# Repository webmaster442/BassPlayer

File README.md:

# BassPlayer

An Audio Player based on bass.dll components & a Total Commander lister plugin.

Compiled binary can be downloaded from: https://drive.google.com/folderview?id=0BzRxNHSnXbB5fjc0bHhQZU4tWXhuWFFHWDBHcWtfVzgtRnJ0d2lVZURTMXZnUmtfV1UwNmc&usp=sharing 

##Features

 - Supports various audio formats: MP3, MP4, AAC, OGG, WAV, FLAC, WavPack, Apple Lossless (ALAC), WMA, AC3, CDDA
 - Supports various playlist formats: PLS, M3U, WPL (Windows Media Player playlists), BPL (Player's native playlist format)
 - 32 bit and 64 bit support
 - Integrated file browser
 - Supports browsing of iTunes database (iTunes required)
 - Supports Windows 7 & 8 Shell features: Taskbar progress & Taskbar preview buttons
 - Supports Keyboard media keys
 - Media Library
 - Mini Player view
 - Audio Converter tools
 
## Required tools to compile
 - Visual Studio Community edition
 - Bass.net API -> http://bass.radio42.com/

##Requirements to run
 - .NET Framework 4.5 (Window7 & Windows8 & Windows 8.1)
   http://www.microsoft.com/hu-hu/download/details.aspx?id=30653

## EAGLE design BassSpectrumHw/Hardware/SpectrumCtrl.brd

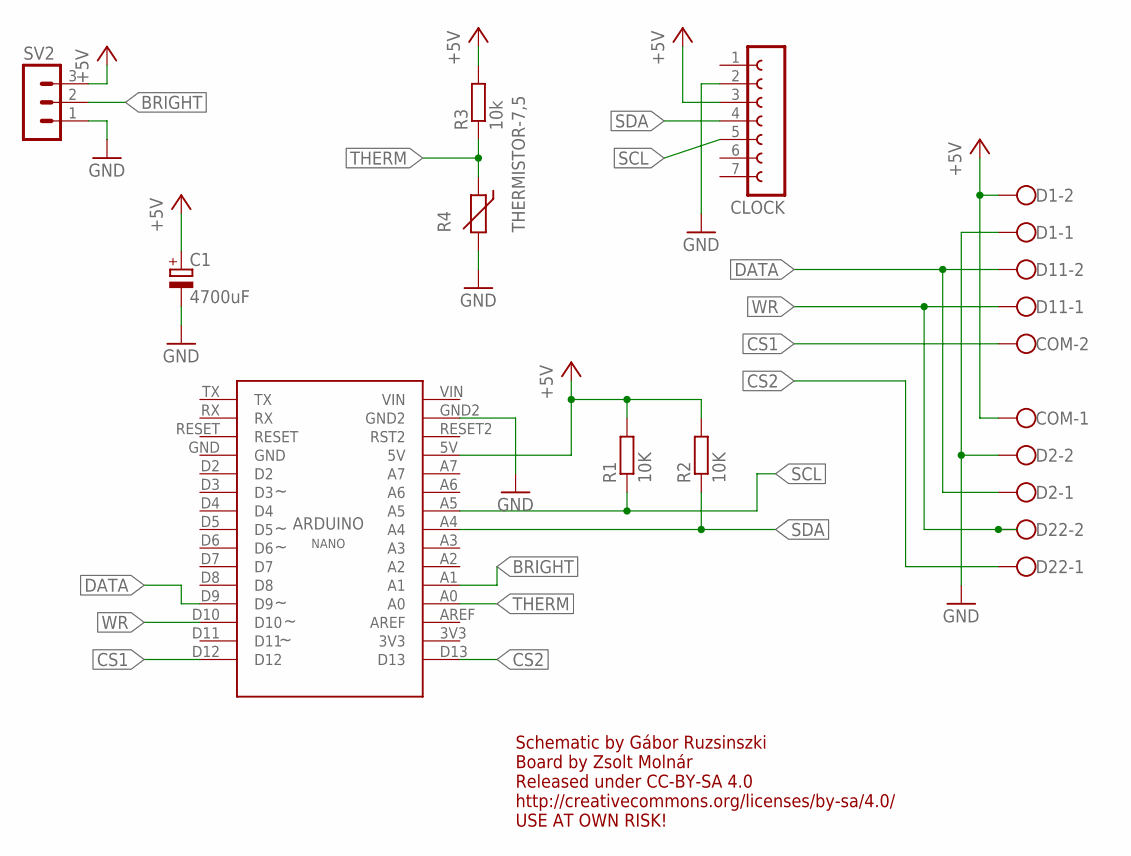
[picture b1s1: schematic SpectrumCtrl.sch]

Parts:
C1: 4700uF; E7,5-16
CLOCK: FE07-1; FE07
COM: W237-102
D1, D2, D11, D22: W237-102
R1, R2: 10K; 0309/12
R3: 10k; 0309/12
R4: THERMISTOR-7,5; R-7,5
SV2: MA03-1
U$1: NANO

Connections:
+5V: C1.+, CLOCK.3, COM.1, D1.2, R1.2, R2.2, R3.2, SV2.3, U$1.5V
BRIGHT: SV2.2, U$1.A1
CS1: COM.2, U$1.D12
CS2: D22.1, U$1.D13
DATA: D2.1, D11.2, U$1.D9
GND: C1.-, CLOCK.2, D1.1, D2.2, R4.2, SV2.1, U$1.GND2
SCL: CLOCK.5, R1.1, U$1.A5
SDA: CLOCK.4, R2.1, U$1.A4
THERM: R3.1, R4.1, U$1.A0
WR: D11.1, D22.2, U$1.D10

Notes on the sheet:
Schematic by Gábor Ruzsinszki Board by Zsolt Molnár Released under CC-BY-SA 4.0 http://creativecommons.org/licenses/by-sa/4.0/ USE AT OWN RISK!

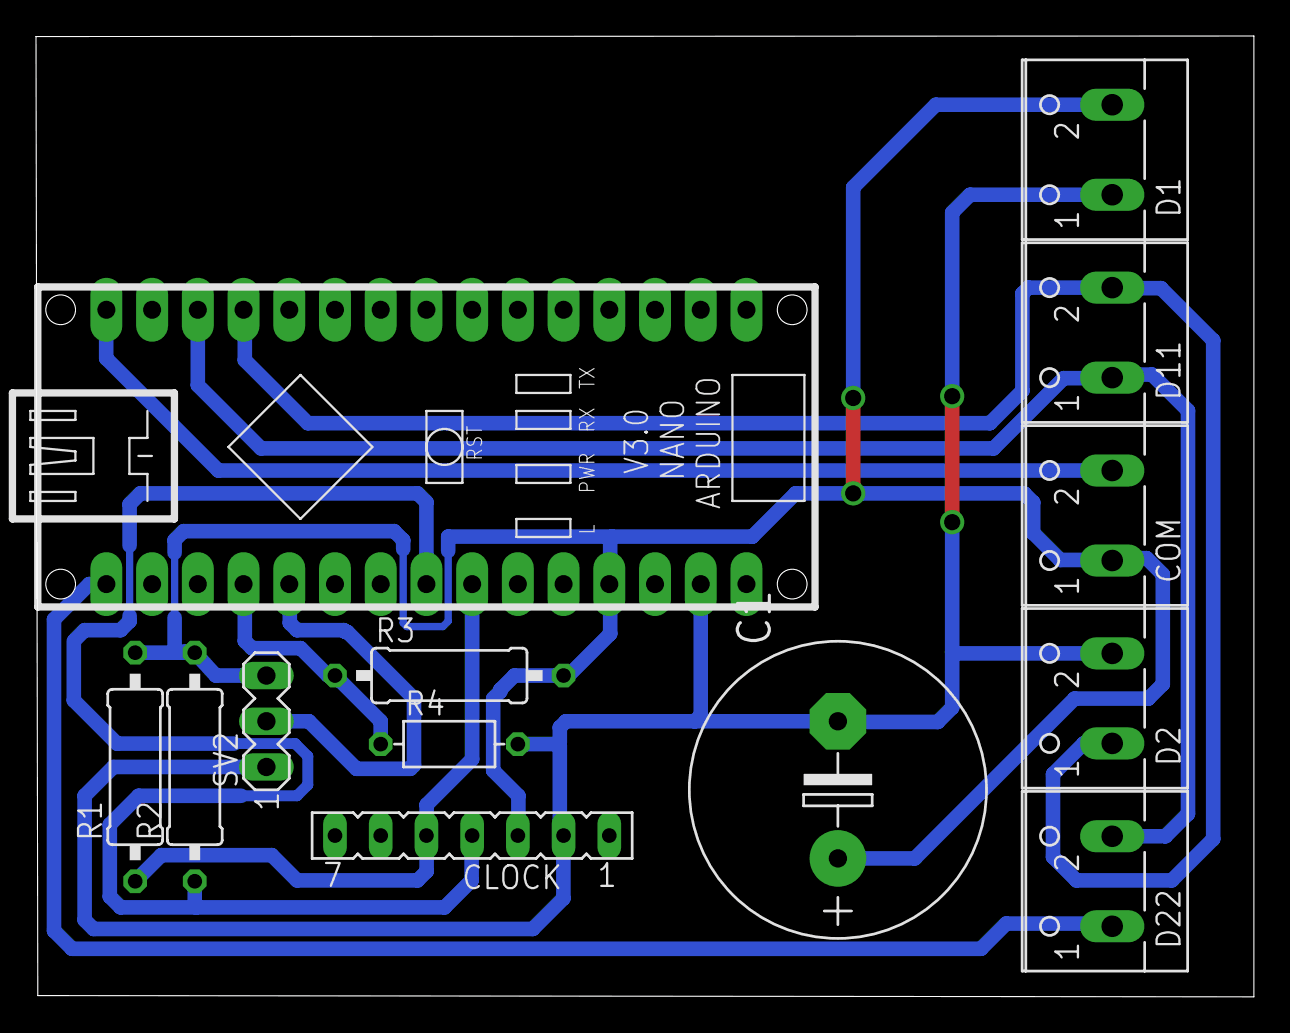
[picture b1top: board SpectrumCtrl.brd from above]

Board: 2 copper layers, 67.7 x 53.4 mm, 13 parts (0 on the bottom side), 10 nets.

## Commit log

2015-01-17 Initial version
2015-01-18 PlayList update & Single Instance
2015-01-18 PlayList updates & icon
2015-01-18 Net streaming support
2015-01-18 URL hotfix
2015-01-19 Audio engine & PlayList updates
2015-01-19 PlayList updates
2015-01-19 YouTubeDownloader lib added Playlist updates initial cd support
2015-01-19 Lister plugin prototypes
2015-01-20 Settings window and application Settings
2015-01-21 BassPlayerLister drop
2015-01-24 Bug fixes & Proxy support
2015-01-24 Design update
2015-01-24 Drag & Drop support
2015-01-25 Folder structure rework & Added total commander lister plugin project
2015-01-25 LICENSE & README.md fix
2015-01-25 Design updates & file load fix
2015-01-28 About dialog, PlayList & Engine bugs fix
2015-01-28 Youtube importer initial work & context menus
2015-01-30 itunes initial support
2015-01-30 iTunes support
2015-01-31 Various Bugfixes Taskbar controls Youtube import
2015-02-01 Small bugfixes, released as version 1.0 beta
2015-02-01 Readme update
2015-02-02 OSD control & song positioning fix
2015-02-02 Lister project updated, C++ runtime is set to static linking
2015-02-02 Added simple visual
2015-02-03 iTunes update
2015-02-04 Look & feel update
2015-02-04 Chapterize functions
2015-02-04 Global KeyboardHook for media keys
2015-02-04 Playlist Async loading
2015-02-04 PlayList design update & small bugfixes
2015-02-05 Source code of version 1.0
2015-02-08 Audio Converter app intitial commit
2015-02-08 Small changes
2015-02-08 sln delete fix
2015-02-09 Converter progress
2015-02-09 Audio converter basicly works
2015-02-10 MediaKey usage as option & better media key error text
2015-02-10 Mp3 converter
2015-02-15 Audio Converter app removed Playlist improvements: phase 1
2015-02-15 File browser update
2015-02-15 Initial work on recent list
2015-02-16 Recents added to PlayList
2015-02-17 PlayList updated to command architecture
2015-02-17 PlayList updates & Device copy support
2015-02-17 Source code of 1.1
2015-02-18 Dead code removal & small patches
2015-02-18 Youtube initial work
2015-02-19 YoutubeExtractor added
2015-02-19 Working Youtube support
2015-02-20 Source rework
2015-02-23 Volume slider change
2015-02-23 iTunes parser update
2015-02-24 Updates from master branch
2015-02-25 Build Error fix
2015-02-25 Project Structure rework part1
2015-02-25 Project Structure rework part2
2015-02-25 Project Structure rework part3
2015-02-25 Spectrum daemon initial work
2015-02-26 Spectrum Hardware firmware added
2015-02-27 Compile error fixes
2015-02-27 Temperature sensing & brightness adjust
2015-02-27 Font size change
2015-02-28 Audio Spectrum Daemon work
2015-02-28 Create gh-pages branch via GitHub
2015-02-28 Spectrum Daemon work
2015-03-01 Spectrum daemon updates
2015-03-02 Spectrum update
2015-03-02 Spectrum app & fw working
2015-03-03 Small code improvements
2015-03-03 Code improvements
2015-03-03 Pages update
2015-03-03 BassConverter Project template
2015-03-04 BassConverter renamed to FFConverter
2015-03-04 FFConverter updates
2015-03-04 Proxy error fix
2015-03-08 Keys update iTunes Playlist support
2015-03-08 FFConverter changes
2015-03-12 Project structure rework TagLib added to engine Player now uses TagLib
2015-03-13 MediaLib updates
2015-03-13 Small updates & fixes
2015-03-14 MiniPlayer added
2015-03-15 FFConverter work BsssPlayer MediaLib progress
2015-03-15 FFConverter work in progress. Currently broken PresetCompiler
2015-03-16 FFConverter updates MediaLib updates
2015-03-16 MediaLib progress
2015-03-18 AlbumArtStorage rework MediaLibTree control added
2015-03-18 MediaLibTree replaces iTunes navigation
2015-04-06 MediaLib now working
2015-04-07 MediaLib fixes & features update added Years view to iTunes view
2015-04-16 FFConverter update with more presets
2015-04-16 Audio converter tools added
2015-04-18 Youtube downloader & small improvements
2015-04-19 Begin work on FFConverterPacker
2015-04-19 Removed FFConverterPacker, because total commander plugin API sucks
2015-06-29 Bugfixes
2015-07-17 AudioSpectrum code updated
2015-07-17 Fixed temperature code
2015-07-21 Added Hardware schematics & board
2015-09-16 Display brightness setting now works in all display modes
2015-11-17 Removed dead stuff
2015-11-17 Removed YoutubeDL dependencies
2015-11-17 Restored default window style
2015-11-17 UI now uses MahApps
